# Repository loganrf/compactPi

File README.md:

# compactPi

compactPi is a project to develop a compact Raspberry Pi Compute Module carrier suitable for ArduPilot applications. It's primarily targeted at marine applications (ArduSub/ArduRover).

## Milestones

As of June 2026, these milestones are way out of date due to personal circumstances. As I get back up to speed there will be substantial updates to this timeline!

| # | Description | Estimated Time Frame| Status |
|---|---|---|---|
| 1 |Feature freeze | Mid-Feb | On Track |
| 2 |Schematic/layout draft ready for review | Early march | In Work |
| 3 |Gerbers ready for review | End of march | TBD |
| 4 |PCB Tape Out | Mid April | TBD |
| 5 |Board Fab & Build | June/July (assuming 30 day turn for initial prototypes to keep costs maneagable)| TBD |
| 6 |Validation/Verification Complete| TBD | TBD |
| 7 |V1.0 Design File Release| TBD (dependent on how well the first rev does) | TBD |

# Layout Study (PRELIMINARY)

# Design Details (PROPOSED)

## Power/Physical
| # | Description | Value/Units | Notes |
|---|---|---|---|
| 1 |Input Voltage range| 6-25V | 2 independent inputs + USB-C PD option |
| 2 |Mainboard power dissipation | 25W | |
| 3 |Dimensions | 45mm x 105mm | Evaluating options for shrinking length without over-crowding connectors|

## Key Sensors
| # | Description | Part Number | 
|---|---|---|
| 1 |6 Axis IMU | ICM-20602 |
| 2 |3 Axis Magnetometer | MMC5983 |
| 3 |3 Axis Compass | AK09915 |
| 4 |Barometer | BMP280 |
| 5 |ADC | TBD |

## Interfaces
| # | Description | Form Factor | Qty | Notes |
|---|---|---|---|---|
| 1 |UART | JST-GH BM06B | 2 |  |
| 2 |I2C | JST-GH BM04B | 2 |  |
| 3 |SBUS | TBD |1| |
| 4 |5V PWM Quad Out | JST-GH BM06B | 4 | 4 PWM channels per connector, 16 total per carrier|
| 5 |Leak Sensor | JST-GH BM02B | 1 | |
| 6 |ADC | TBD | TBD| |
| 7 |HDMI | HDMI-C | 1 | |
| 8 |Ethernet 10/100| JST-GH BM04B | 1 | |
| 9 |USB| 1x JST-GH BM04B/ 1x USB-C OTG | 2 | |
| 10 |SD| micro-SD | 1 | |
| 11 |Power | TBD | 2 | |
| 12 |CAN Bus | JST-GH BM04B | 2 | |

# Stackup

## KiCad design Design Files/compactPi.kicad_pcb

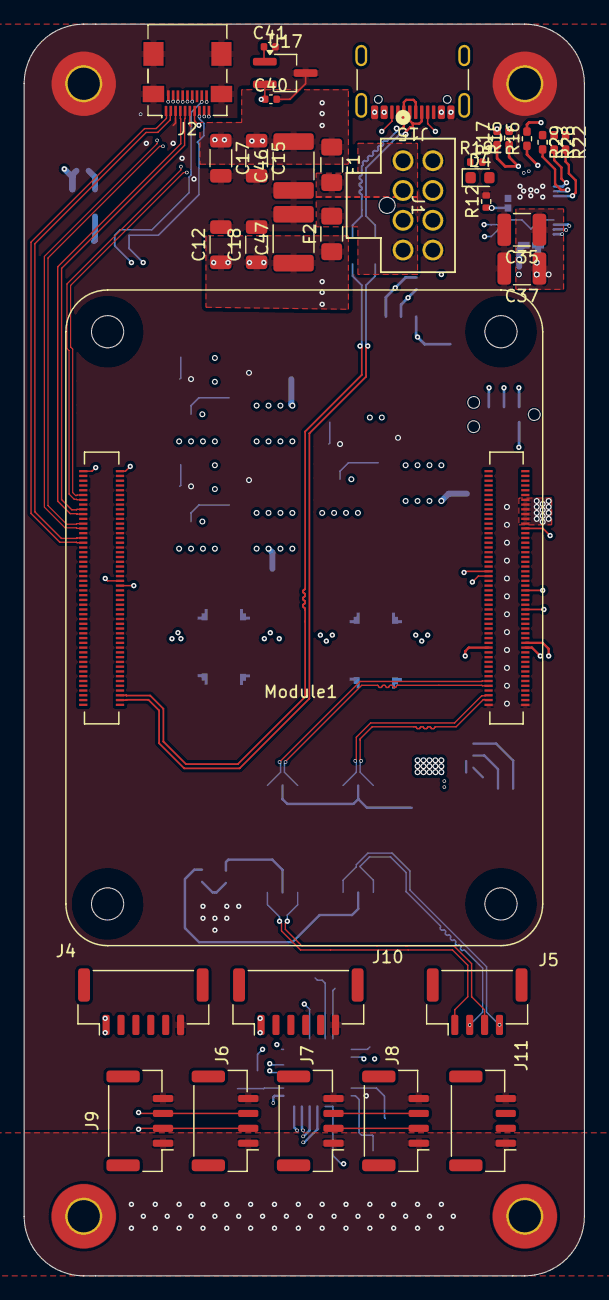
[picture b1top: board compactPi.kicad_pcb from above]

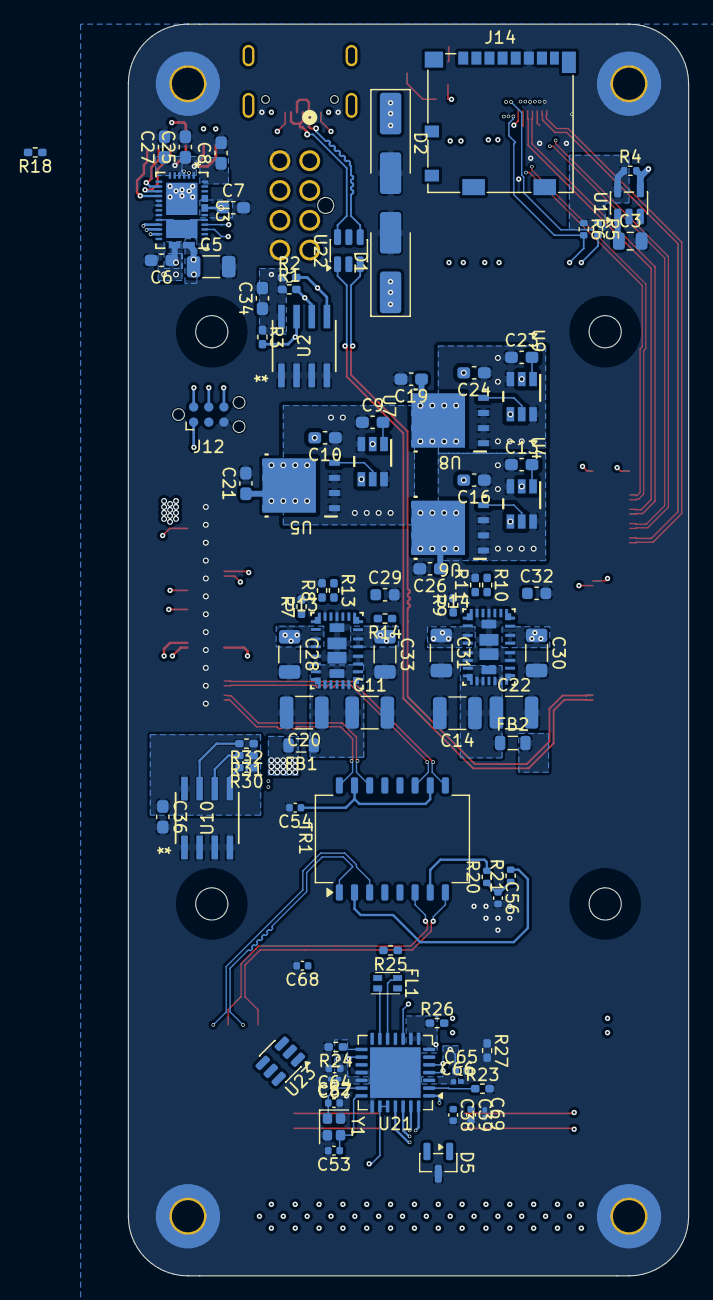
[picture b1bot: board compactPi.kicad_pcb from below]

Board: 6 copper layers, 47.0 x 105.0 mm, 127 parts (89 on the bottom side), 107 nets.

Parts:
C3: 10u; C_0805_2012Metric
C5, C12, C15, C17, C18, C28, C30, C31, C33: 4.7uF; C_1206_3216Metric
C6, C25, C27: 10uF; C_0603_1608Metric_Pad1.08x0.95mm_HandSolder
C7, C8, C9, C10, C13, C16, C19, C21, C23, C24, C26, C34, C36: 100nF; C_0603_1608Metric_Pad1.08x0.95mm_HandSolder
C11, C14, C20, C22: 47uF; C_1210_3225Metric
C29, C32: 1uF; C_0603_1608Metric
C35, C37: 22uF; C_1210_3225Metric
C38, C39, C54, C64, C65: 100nF; C_0402_1005Metric
C40, C41: 100n; C_0402_1005Metric
C46, C47: 6.8uF; C_1812_4532Metric
C52, C53: 22pF; C_0402_1005Metric
C56: 1000pF; C_0402_1005Metric
C66, C67, C69: 10u; C_0201_0603Metric
C68: 47pF; C_0402_1005Metric
D1, D2: SMAJ26A; D_SMA_Handsoldering
D4: LED Red; LED_0603_1608Metric
D5: SZNUP2105L; SOT-23
F1, F2: 10A; Fuse_1206_3216Metric_Pad1.42x1.75mm_HandSolder
FB1, FB2: FerriteBead_Small; L_0805_2012Metric
FL1: Choke_CommonMode_FerriteCore_1234; L_CommonModeChoke_Coilcraft_0805USB
H1, H2, H3, H4: MountingHole_Pad; MountingHole_2.7mm_Pad_TopBottom
J1: 1053101208; CONN_SD-105310-100_08_MOL
J2: HDMI_A_1.4; HDMI_Micro-D_Molex_46765-0xxx
J4, J10: Conn_01x06_MountingPin; JST_GH_BM06B-GHS-TBT_1x06-1MP_P1.25mm_Vertical
J5, J6, J7, J8, J9, J11: Conn_01x04_MountingPin; JST_GH_BM04B-GHS-TBT_1x04-1MP_P1.25mm_Vertical
J12: Conn_ARM_SWD_TagConnect_TC2030-NL; Tag-Connect_TC2030-IDC-NL_2x03_P1.27mm_Vertical
J14: Micro_SD_Card_Det; microSD_HC_Molex_104031-0811
J15: USB_C_Receptacle_USB2.0; USB_C_Receptacle_GCT_USB4105-xx-A_16P_TopMnt_Horizontal
Module1: ComputeModule5-CM5; Raspberry-Pi-5-Compute-Module
R1, R2, R3, R22, R28, R29, R30, R31, R32: 4.7k; R_0402_1005Metric_Pad0.72x0.64mm_HandSolder
R4: 10K 1%; R_0402_1005Metric
R5, R6: 2.2K 1%; R_0402_1005Metric
R7, R9: 25.5k; R_0402_1005Metric_Pad0.72x0.64mm_HandSolder
R8, R11, R14, R15, R16, R17, R18, R23, R24, R26, R27: 10k; R_0402_1005Metric_Pad0.72x0.64mm_HandSolder
R10, R13: 39.2k; R_0402_1005Metric_Pad0.72x0.64mm_HandSolder
R12: 10k; R_0402_1005Metric
R19: 1k; R_0402_1005Metric
R20, R21: 75; R_0402_1005Metric
R25: 120; R_0402_1005Metric_Pad0.72x0.64mm_HandSolder
TR1: TG110-E050N5xx; Transformer_Ethernet_Halo_N5_SO-16_7.11x12.7mm
U1: RT9742GGJ5; SOT-23-5
U2, U10: AT24C256C-SSHL-T; 8S1_MCH
U3: WQFN38_REF_TEX
U4, U7, U9: LM74700QDBVRQ1; DBV0006A_M
U5, U6, U8: CSD18511Q5A; DQJ0008A
U13, U14: TLVM13630RDHR; B0QFN30_RDH_TEX
U17: RT9742SNGV; TSOT-23_HandSoldering
U21: MCP25625x-x-ML; QFN-28-1EP_6x6mm_P0.65mm_EP4.25x4.25mm
U22, U23: WE-TVS-82400102; SOT-23-6
Y1: Crystal_GND24_Small; Crystal_SMD_2016-4Pin_2.0x1.6mm

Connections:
/1V8: Module1.88 (+1.8v_(Output)), Module1.90 (+1.8v_(Output))
/3V3: C8.1, C36.1, C38.1, C39.1, C69.1, D4.2 (A), Module1.78 (GPIO_VREF(1.8v/3.3v_Input)), Module1.84 (+3.3v_(Output)), Module1.86 (+3.3v_(Output)), R4.1, R5.1, R6.1, R22.1, R26.2, R27.1, R28.1, R29.1, R30.1, R31.1, R32.1, U1.5 (IN), U3.38 (VIN_3V3), U10.8 (VCC), U21.3 (V_{DD}), U21.11 (V_{IO})
/5V0_CORE: FB1.2, Module1.77 (+5v_(Input)), Module1.79 (+5v_(Input)), Module1.81 (+5v_(Input)), Module1.83 (+5v_(Input)), Module1.85 (+5v_(Input)), Module1.87 (+5v_(Input))
/5V0_PERIPHERAL: C41.1, C64.1, C65.1, C66.1, C67.1, FB2.2, J4.1, J6.1, J7.1, J8.1, J9.1, J10.1, J11.1, U3.34 (PP5V), U3.35 (PP5V), U17.1 (IN), U21.19 (V_{DDA})
/Autopilot Interfaces/CANH_PC: FL1.1, U21.13 (CANH)
/Autopilot Interfaces/CAN_CLKO: C68.1, U21.6 (CLKOUT)
/Autopilot Interfaces/CAN_H: D5.1 (K), FL1.2, J7.2, J8.2, R25.1
/Autopilot Interfaces/CAN_L: D5.2 (K), FL1.4, J7.3, J8.3, R25.2
/Autopilot Interfaces/CAN_L_PC: FL1.3, U21.12 (CANL)
/Autopilot Interfaces/CAN_PULL_HI: R26.1, U21.7 (~Tx0RTS), U21.8 (~Tx1RTS), U21.9 (~Tx2RTS), U21.23 (~Rx1BF), U21.24 (~Rx0BF)
/Autopilot Interfaces/CAN_RST: R23.1, R27.2, U21.2 (~RESET)
/Autopilot Interfaces/CAN_RX: U21.5 (RxCAN), U21.10 (R_{XD})
/Autopilot Interfaces/CAN_STBY: R24.1, U21.15 (STBY)
/Autopilot Interfaces/CAN_TX: U21.4 (TxCAN), U21.16 (T_{XD})
/Autopilot Interfaces/OSC_1: C53.1, U21.21 (OSC1), Y1.3
/Autopilot Interfaces/OSC_2: C52.1, U21.20 (OSC2), Y1.1
/CAN_nINT: Module1.41 (GPIO25), U21.25 (~INT)
/CC1: J15.A5 (CC1), U3.28 (CC1)
/CC2: J15.B5 (CC2), U3.29 (CC2)
/CM5 GPIO Ethernet SDIO/ID_SC: Module1.35 (ID_SC), R31.2, U10.6 (SCL)
/CM5 GPIO Ethernet SDIO/ID_SD: Module1.36 (ID_SD), R30.2, U10.5 (SDA)
/CM5 GPIO Ethernet SDIO/SD_CLK: J14.5 (CLK), Module1.57 (SD_CLK)
/CM5 GPIO Ethernet SDIO/SD_CMD: J14.3 (CMD), Module1.62 (SD_CMD)
/CM5 GPIO Ethernet SDIO/SD_DAT0: J14.7 (DAT0), Module1.63 (SD_DAT0)
/CM5 GPIO Ethernet SDIO/SD_DAT1: J14.8 (DAT1), Module1.67 (SD_DAT1)
/CM5 GPIO Ethernet SDIO/SD_DAT2: J14.1 (DAT2), Module1.69 (SD_DAT2)
/CM5 GPIO Ethernet SDIO/SD_DAT3: J14.2 (DAT3/CD), Module1.61 (SD_DAT3)
/CM5 GPIO Ethernet SDIO/SD_PWR: C3.1, J14.4 (VDD), U1.1 (OUT)
/CM5 GPIO Ethernet SDIO/SD_PWR_ON: Module1.75 (SD_PWR_ON), R4.2, U1.4 (EN)
/CM5 GPIO Ethernet SDIO/TRD0_N: Module1.10 (Ethernet_Pair0_N), TR1.11 (RD-)
/CM5 GPIO Ethernet SDIO/TRD0_P: Module1.12 (Ethernet_Pair0_P), TR1.9 (RD+)
/CM5 GPIO Ethernet SDIO/TRD0_TX_N: J5.3, TR1.6 (RX-)
/CM5 GPIO Ethernet SDIO/TRD0_TX_P: J5.1, TR1.8 (RX+)
/CM5 GPIO Ethernet SDIO/TRD1_N: Module1.6 (Ethernet_Pair1_N), TR1.14 (TD+)
/CM5 GPIO Ethernet SDIO/TRD1_P: Module1.4 (Ethernet_Pair1_P), TR1.16 (TD-)
/CM5 GPIO Ethernet SDIO/TRD1_RX_N: J5.4, TR1.3 (TX+)
/CM5 GPIO Ethernet SDIO/TRD1_RX_P: J5.2, TR1.1 (TX-)
/CM5 GPIO Ethernet SDIO/nPWR_LED: Module1.95 (LED_nPWR), R19.2
/CM5 USB HDMI/HDMI0_CEC: J2.13 (CEC), Module1.151 (HDMI0_CEC)
/CM5 USB HDMI/HDMI0_CK_N: J2.12 (CK-), Module1.190 (HDMI0_CLK_N)
/CM5 USB HDMI/HDMI0_CK_P: J2.10 (CK+), Module1.188 (HDMI0_CLK_P)
/CM5 USB HDMI/HDMI0_D0_N: J2.9 (D0-), Module1.184 (HDMI0_TX0_N)
/CM5 USB HDMI/HDMI0_D0_P: J2.7 (D0+), Module1.182 (HDMI0_TX0_P)
/CM5 USB HDMI/HDMI0_D1_N: J2.6 (D1-), Module1.178 (HDMI0_TX1_N)
/CM5 USB HDMI/HDMI0_D1_P: J2.4 (D1+), Module1.176 (HDMI0_TX1_P)
/CM5 USB HDMI/HDMI0_D2_N: J2.3 (D2-), Module1.172 (HDMI0_TX2_N)
/CM5 USB HDMI/HDMI0_D2_P: J2.1 (D2+), Module1.170 (HDMI0_TX2_P)
/CM5 USB HDMI/HDMI0_HOTPLUG: J2.19 (HPD/HEAC-), Module1.153 (HDMI0_HOTPLUG)
/CM5 USB HDMI/HDMI0_SCL: J2.15 (SCL), Module1.200 (HDMI0_SCL), R6.2
/CM5 USB HDMI/HDMI0_SDA: J2.16 (SDA), Module1.199 (HDMI0_SDA), R5.2
/CM5 USB HDMI/HDMI_5v: C40.1, J2.18 (+5V), U17.2 (OUT)
/CM5 USB HDMI/USB3-1-D_N: Module1.165 (USB3-1-D_N), U23.1
/CM5 USB HDMI/USB3-1-D_P: Module1.163 (USB3-1-D_P), U23.3
/CM5 USB HDMI/USB3-1-Port_N: J11.2, U23.6
/CM5 USB HDMI/USB3-1-Port_P: J11.3, U23.4
/I2C_EXT_SCL1: J6.2, J9.2, Module1.56 (GPIO3)
/I2C_EXT_SDA1: J6.3, J9.3, Module1.58 (GPIO2)
/I2C_PMIC_SCL: Module1.37 (GPIO7), R29.2, U3.9 (I2Ct_SCL)
/I2C_PMIC_SDA: Module1.30 (GPIO6), R28.2, U3.8 (I2Ct_SDA)
/I2C_PMIC_nINT: Module1.24 (GPIO26), R22.2, U3.10 (nI2Ct_IRQ)
/Power/5V0_C_FB: R8.1, R13.2, U13.25 (FB)
/Power/5V0_C_RAW: C11.1, C20.1, FB1.1, R13.1, U13.7 (VOUT), U13.8 (VOUT), U13.9 (VOUT), U13.10 (VOUT), U13.12 (VOUT), U13.13 (VOUT), U13.14 (VOUT), U13.15 (VOUT), U13.22 (VLDOIN), U13.30 (VOUT)
/Power/5V0_C_RT: R7.1, U13.1 (RT)
/Power/5V0_C_VCC: C29.1, U13.23 (VCC)
/Power/5V0_EN: R14.2, U13.2 (EN/SYNC)
/Power/5V0_P_FB: R10.2, R11.1, U14.25 (FB)
/Power/5V0_P_RAW: C14.1, C22.1, FB2.1, R10.1, U14.7 (VOUT), U14.8 (VOUT), U14.9 (VOUT), U14.10 (VOUT), U14.12 (VOUT), U14.13 (VOUT), U14.14 (VOUT), U14.15 (VOUT), U14.22 (VLDOIN), U14.30 (VOUT)
/Power/5V0_P_RT: R9.1, U14.1 (RT)
/Power/5V0_P_VCC: C32.1, U14.23 (VCC)
/Power/EEPROM_WP: J12.6 (SWO), R3.2, U2.7 (WP)
/Power/G_AUX: U4.5 (GATE), U6.4 (G)
/Power/G_BATT: U5.4 (G), U7.5 (GATE)
/Power/G_USB: U8.4 (G), U9.5 (GATE)
/Power/I2Cc_SCL: J12.4 (SWCLK), R1.2, U2.6 (SCL), U3.17 (I2Cc_SCL)
/Power/I2Cc_SDA: J12.2 (SWDIO), R2.2, U2.5 (SDA), U3.16 (I2Cc_SDA)
/Power/LDO_1V5: C27.1, R16.1, U3.4 (LDO_1V5)
/Power/USB_DRAIN: U3.15 (DRAIN), U3.30 (DRAIN), U3.40 (DRAIN_PAD)
/Power/USB_LDO_3V3: C25.1, C34.1, J12.1 (VCC), R1.1, R2.1, R3.1, R15.1, R17.1, U2.8 (VCC), U3.1 (LDO_3V3)
/Power/VCAP_AUX: C13.2, U4.1 (VCAP)
/Power/VCAP_BATT: C9.2, U7.1 (VCAP)
/Power/VCAP_USB: C23.2, U9.1 (VCAP)
/Power/V_AUX: C12.1, C13.1, C16.1, C18.1, C47.1, D1.1 (A1), F2.1, U4.3 (EN), U4.6 (ANODE), U6.1 (S), U6.2 (S), U6.3 (S)
/Power/V_BATT: C9.1, C10.1, C15.1, C17.1, C46.1, D2.1 (A1), F1.1, U5.1 (S), U5.2 (S), U5.3 (S), U7.3 (EN), U7.6 (ANODE)
/Power/V_COMMON: C19.1, C21.1, C26.1, C28.1, C30.1, C31.1, C33.1, R14.1, U4.4 (CATHODE), U5.5 (D), U5.6 (D), U5.7 (D), U5.8 (D), U5.9 (D), U6.5 (D), U6.6 (D), U6.7 (D), U6.8 (D), U6.9 (D), U7.4 (CATHODE), U8.5 (D), U8.6 (D), U8.7 (D), U8.8 (D), U8.9 (D), U9.4 (CATHODE), U13.3 (VIN), U13.4 (VIN), U13.18 (VIN), U13.19 (VIN), U14.3 (VIN), U14.4 (VIN), U14.18 (VIN), U14.19 (VIN)
/Power/V_USB: C6.1, C23.1, C24.1, C35.1, C37.1, U3.20 (PPHV), U3.21 (PPHV), U3.22 (PPHV), U8.1 (S), U8.2 (S), U8.3 (S), U9.3 (EN), U9.6 (ANODE)
/SPI_CAN_CE0: Module1.49 (GPIO18), U21.1 (~CS)
/SPI_CAN_CIPO: Module1.26 (GPIO19), U21.28 (SO)
/SPI_CAN_COPI: Module1.27 (GPIO20), U21.27 (SI)
/SPI_CAN_SCK: Module1.25 (GPIO21), U21.26 (SCK)
/USB2_N: J15.A7 (D-), J15.B7 (D-), U22.6
/USB2_P: J15.A6 (D+), J15.B6 (D+), U22.4
/USB2a_N: Module1.103 (USB2_N), U22.1
/USB2a_P: Module1.105 (USB2_P), U22.3
/VBUS: C5.1, C7.1, J15.A4 (VBUS), J15.A9 (VBUS), J15.B4 (VBUS), J15.B9 (VBUS), R12.1, U3.23 (VBUS_IN), U3.24 (VBUS_IN), U3.25 (VBUS_IN), U3.32 (VBUS), U3.33 (VBUS)
/VBUS_EN: Module1.111 (VBUS_EN), R18.1, U14.2 (EN/SYNC)
GND: C3.2, C5.2, C6.2, C7.2, C8.2, C10.2, C11.2, C12.2, C14.2, C15.2, C16.2, C17.2, C18.2, C19.2, C20.2, C21.2, C22.2, C24.2, C25.2, C26.2, C27.2, C28.2, C29.2, C30.2, C31.2, C32.2, C33.2, C34.2, C35.2, C36.2, C37.2, C38.2, C39.2, C40.2, C41.2, C46.2, C47.2, C52.2, C53.2, C54.2, C56.2, C64.2, C65.2, C66.2, C67.2, C68.2, C69.2, D1.2 (A2), D2.2 (A2), D5.3 (A), H1.1 (1_1), H2.1 (1_1), H3.1 (1_1), H4.1 (1_1), J1.5, J1.8, J2.2 (D2S), J2.5 (D1S), J2.8 (D0S), J2.11 (CKS), J2.17 (GND), J2.SH, J4.6, J6.4, J7.4, J8.4, J9.4, J10.6, J11.4, J12.5 (GND), J14.6 (VSS), J15.A1 (GND), J15.A12 (GND), J15.B1 (GND), J15.B12 (GND), Module1.1 (GND), Module1.2 (GND), Module1.7 (GND), Module1.8 (GND), Module1.13 (GND), Module1.14 (GND), Module1.22 (GND), Module1.23 (GND), Module1.32 (GND), Module1.33 (GND), Module1.42 (GND), Module1.43 (GND), Module1.52 (GND), Module1.53 (GND), Module1.59 (GND), Module1.60 (GND), Module1.65 (GND), Module1.66 (GND), Module1.71 (GND), Module1.74 (GND), Module1.98 (GND), Module1.107 (GND), Module1.108 (GND), Module1.113 (GND), Module1.114 (GND), Module1.119 (GND), Module1.120 (GND), Module1.125 (GND), Module1.126 (GND), Module1.131 (GND), Module1.132 (GND), Module1.137 (GND), Module1.138 (GND), Module1.144 (GND), Module1.150 (GND), Module1.155 (GND), Module1.156 (GND), Module1.161 (GND), Module1.162 (GND), Module1.167 (GND), Module1.168 (GND), Module1.173 (GND), Module1.174 (GND), Module1.179 (GND), Module1.180 (GND), Module1.185 (GND), Module1.186 (GND), Module1.191 (GND), Module1.192 (GND), Module1.197 (GND), Module1.198 (GND), R7.2, R8.2, R9.2, R11.2, R12.2, R18.2, R23.2, R24.2, U1.2 (GND), U2.1 (A0), U2.2 (A1), U2.3 (A2), U2.4 (GND), U3.11 (GND), U3.12 (GND), U3.14 (GND), U3.31 (GND), U3.39 (GND), U4.2 (GND), U7.2 (GND), U9.2 (GND), U10.1 (A0), U10.2 (A1), U10.3 (A2), U10.4 (GND), U13.5 (PGND), U13.6 (PGND), U13.16 (PGND), U13.17 (PGND), U13.24 (AGND), U13.26 (PG), U13.27 (AGND), U13.28 (PGND), U13.29 (PGND), U14.5 (PGND), U14.6 (PGND), U14.16 (PGND), U14.17 (PGND), U14.24 (AGND), U14.26 (PG), U14.27 (AGND), U14.28 (PGND), U14.29 (PGND), U17.3 (GND), U21.18 (V_{SS}), U21.22 (GND), U21.29 (EP), Y1.2 (G), Y1.4 (G)
unnamed: C56.1, R20.1, R21.1
unnamed: D4.1 (K), R19.1
unnamed: F1.2, J1.1
unnamed: F2.2, J1.4
unnamed: C54.1, TR1.10 (C_RD), TR1.15 (C_TD)
unnamed: R20.2, TR1.7 (C_RX)
unnamed: R21.2, TR1.2 (C_TX)
unnamed: R15.2, U3.2 (ADCIN1)
unnamed: R16.2, U3.3 (ADCIN2)
unnamed: R17.2, U3.18 (nI2Cc_IRQ)
unnamed: R32.2, U10.7 (WP)

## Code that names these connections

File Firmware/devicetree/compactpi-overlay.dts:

// SPDX-License-Identifier: CERN-OHL-S-2.0
/*
 * compactpi-overlay.dts — Device-tree overlay for the compactPi CM5 carrier
 *
 * Covers the on-board peripherals that need explicit DT description.
 * Everything else (HDMI0, microSD on CM5 Lite, USB host on USB3-1 D±,
 * Ethernet PHY, I2C1 pull-ups, PWR LED) is handled by the stock
 * bcm2712-rpi-cm5*.dtb and needs no overlay.
 *
 * Schematic reference: compactPi rev 0, commit f49593c + working-tree edits (2026-10-19)
 *
 *   Peripheral                 CM5 signal            Status
 *   -------------------------  --------------------  ---------------------------
 *   5V0_PERIPHERAL rail (U14)  VBUS_EN (RP1 GPIO42)  described below (regulator)
 *   MCP25625 CAN (U21)         SPI1 CE0, INT=GPIO25  described below
 *   I2C1 ext. (J6, J9)         GPIO2/3               enabled via config.txt
 *   Ethernet 10/100 (J5)       2-pair magnetics      PHY capped at 100 Mb/s below
 *   USB-C (J15) device port    USB2 OTG, ID floating dwc2 peripheral via config.txt
 *   UART J4 / J10              — not yet wired —     placeholders in config.txt
 *   TPS25751 I2Ct (U3)         GPIO6/7 = RP1 I2C3,   bus via config.txt (i2c3-pi5);
 *                              IRQ = GPIO26          IRQ pull-up below; no kernel driver
 *                                                    bound (userspace, address 0x20)
 *
 * Build:   dtc -@ -I dts -O dtb -o compactpi.dtbo compactpi-overlay.dts
 * Install: sudo cp compactpi.dtbo /boot/firmware/overlays/
 *          then add  dtoverlay=compactpi  to /boot/firmware/config.txt
 */

/dts-v1/;
/plugin/;

/* Plain constants so the file builds with dtc alone (no cpp/dt-bindings):
 *   GPIO_ACTIVE_HIGH = 0, IRQ_TYPE_LEVEL_LOW = 8 */

/ {
	compatible = "brcm,bcm2712";

	/* ------------------------------------------------------------------
	 * 1. Peripheral 5 V rail (U14 TLVM13630, EN <- CM5 VBUS_EN / RP1 GPIO42)
	 *    Feeds MCP25625 VDDA, J4/J6-J10 VCC, J11 USB-host VBUS, HDMI 5 V,
	 *    TPS25751 PP5V.  R18 pulls EN low until RP1 drives it.
	 *
	 *    VERIFY ON TARGET: the stock CM5 DTB may already own GPIO42 for
	 *    USB VBUS control.  Check with `pinctrl get 42` / `gpioinfo` before
	 *    relying on this node; if it is already driven high by firmware,
	 *    delete fragment@0 and drop the xceiver-supply reference below.
	 * ------------------------------------------------------------------ */
	fragment@0 {
		target-path = "/";
		__overlay__ {
			compactpi_periph_5v: compactpi-periph-5v {
				compatible = "regulator-fixed";
				regulator-name = "5V0_PERIPHERAL";
				regulator-min-microvolt = <5000000>;
				regulator-max-microvolt = <5000000>;
				gpio = <&rp1_gpio 42 0>;
				enable-active-high;
				startup-delay-us = <5000>;   /* TLVM13630 soft-start + margin */
				regulator-boot-on;
				regulator-always-on;         /* JST VCC pins, USB host, HDMI 5V */
			};
		};
	};

	/* ------------------------------------------------------------------
	 * 2. MCP25625 oscillator (Y1)
	 *    Y1 HAS NO VALUE IN THE SCHEMATIC YET.  16 MHz assumed; change
	 *    clock-frequency (or use dtparam=can_oscillator=...) to match.
	 * ------------------------------------------------------------------ */
	fragment@1 {
		target-path = "/";
		__overlay__ {
			compactpi_can_osc: compactpi-can-osc {
				compatible = "fixed-clock";
				#clock-cells = <0>;
				clock-frequency = <16000000>;
			};
		};
	};

	/* ------------------------------------------------------------------
	 * 3. SPI1 (RP1): GPIO21 SCLK, GPIO20 MOSI -> U21 SI, GPIO19 MISO <- U21 SO,
	 *    GPIO18 CE0 -> U21 ~CS.  CE1 (GPIO17) unused.
	 *    The bus itself is enabled by `dtoverlay=spi1-1cs,cs0_spidev=off`
	 *    in config.txt; this fragment only adds the CAN controller to it.
	 * ------------------------------------------------------------------ */
	fragment@2 {
		target = <&spi1>;
		__overlay__ {
			#address-cells = <1>;
			#size-cells = <0>;
			status = "okay";

			compactpi_can0: can@0 {
				compatible = "microchip,mcp25625";
				reg = <0>;                          /* CE0 */
				spi-max-frequency = <10000000>;     /* MCP25625 max 10 MHz */
				clocks = <&compactpi_can_osc>;
				interrupt-parent = <&rp1_gpio>;
				interrupts = <25 8>;   /* CAN_nINT, GPIO25 */
				pinctrl-names = "default";
				pinctrl-0 = <&compactpi_can_int_pins>;
				/* VDD/VIO are CM5 +3V3 (always on with the module): no vdd-supply */
				xceiver-supply = <&compactpi_periph_5v>;  /* VDDA, 5 V */
				status = "okay";
			};
		};
	};

	/* ------------------------------------------------------------------
	 * 4. GPIO25 as interrupt input with pull-up (MCP25625 ~INT)
	 * ------------------------------------------------------------------ */
	fragment@3 {
		target = <&rp1_gpio>;
		__overlay__ {
			compactpi_can_int_pins: compactpi-can-int-pins {
				pins = "gpio25";
				function = "gpio";
				bias-pull-up;
			};
		};
	};

	/* ------------------------------------------------------------------
	 * 5. Ethernet: only pairs 0/1 are wired (TG110 10/100 magnetics),
	 *    so stop the BCM54210PE advertising 1000BASE-T.
	 *    VERIFY label: in current Raspberry Pi kernels the CM5 PHY node is
	 *    `phy1` under `rp1_eth`; adjust if `dtc -I fs /proc/device-tree`
	 *    shows otherwise.
	 * ------------------------------------------------------------------ */
	fragment@4 {
		target = <&phy1>;
		__overlay__ {
			max-speed = <100>;
		};
	};

	/* ------------------------------------------------------------------
	 * 6. TPS25751 I2Ct interrupt (nI2Ct_IRQ, open-drain) -> GPIO26.
	 *    Bus: RP1 I2C3 on GPIO6 (SDA) / GPIO7 (SCL), enabled by
	 *    `dtoverlay=i2c3-pi5,pins_6_7` in config.txt -> /dev/i2c-3.
	 *    Target address 0x20 (ADCIN1=7 / ADCIN2=5, index #1).
	 *    No kernel driver is bound: mainline tps6598x knows "ti,tps25750"
	 *    but not the TPS25751, and the board loads its config from EEPROM.
	 *    Access it from userspace (i2c-tools) instead.
	 * ------------------------------------------------------------------ */
	fragment@5 {
		target = <&rp1_gpio>;
		__overlay__ {
			compactpi_pd_irq_pins: compactpi-pd-irq-pins {
				pins = "gpio26";
				function = "gpio";
				bias-pull-up;
			};
		};
	};

	__overrides__ {
		can_oscillator = <&compactpi_can_osc>, "clock-frequency:0";
		can_spi_hz     = <&compactpi_can0>, "spi-max-frequency:0";
		can            = <&compactpi_can0>, "status";
		eth_max_speed  = <&phy1>, "max-speed:0";
	};
};

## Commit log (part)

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2026-01-23 Add licensing information to LICENSE.md
2026-01-23 Update hardware license from CERN-OHL-S-2.0 to CERN-OHL-W-2.0
    Updated to weak variant of CERN hardware license. Derivative products do not need to be reciprocally licensed.
2026-01-23 added hardware directory
2026-01-23 Add CERN Open Hardware Licence Version 2
    Added CERN Open Hardware Licence Version 2 - Weakly Reciprocal to the project.
2026-01-23 began stubbing out readme
2026-01-25 Revise design details and specifications in README
    Updated design details and specifications for the compactPi project, including power, physical dimensions, key sensors, and interfaces.
2026-01-25 Add CAN Bus entry to the README table
2026-01-26 Add layout study section with images
    Added preliminary layout study images to README.
2026-01-26 Add milestones section to README
    Added milestones section with estimated time frames and statuses for project development.
2026-02-02 Updated input voltage range to reflect dropout voltage of the power architecture (6V instead of 5V)
2026-02-02 Added to gitignore
2026-02-08 Initial design file commit
2026-02-08 file reorg
2026-02-09 Added additional ground vias to ethernet nets
2026-02-10 Added stackup
2026-02-10 Add signal integrity review findings for HDMI, USB, and Ethernet
    Conducted a detailed analysis of the high-speed nets in the KiCad layout.
    Identified several significant signal integrity issues, including:
    - Excessive length mismatch in HDMI0_D0 differential pair (~6mm).
    - Inconsistent via usage and trace width variations in HDMI lanes.
    - Unrouted high-speed interfaces (USB 3.0/3.1, PCIE, MIPI) that are defined in the schematic.
    - Sub-optimal length matching in Ethernet TRD0 pair.
2026-02-10 updated skews
2026-03-02 Prelim work on autopilot sensors complete
2026-03-02 Fixed reversed I2C tranlator
2026-03-12 Continued adding GPIO interfaces
2026-03-15 More interface interconnects
2026-03-15 Fixed power & GPIO nets
    Added PWM I2C Bus
    Replaced global power labels on the sensor page with hierarchical pins & page labels
    Cleaned up CM5 GPIO block sheet
2026-03-31 Additional layout updates
2026-03-31 Provisional CAN interface design/layout. Probably need to move more north
2026-06-13 SD pwr routed
2026-06-13 Misc
2026-06-22 Updating to reflect restarting the project

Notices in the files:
Design Files/compactPi.kicad_pcb:
Licensed under CERN-OHL-S v2
Copyright © 2026 Logan Fagg
